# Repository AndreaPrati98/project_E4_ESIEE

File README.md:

# project_E4_ESIEE

The code for using the sensors and all is: _project_E4_ESIEE/Rendu_code/code_wio/code_final.wio/code_final.wio.ino_

The other files are experiments and trials to get the confidence with the WIO Terminal.

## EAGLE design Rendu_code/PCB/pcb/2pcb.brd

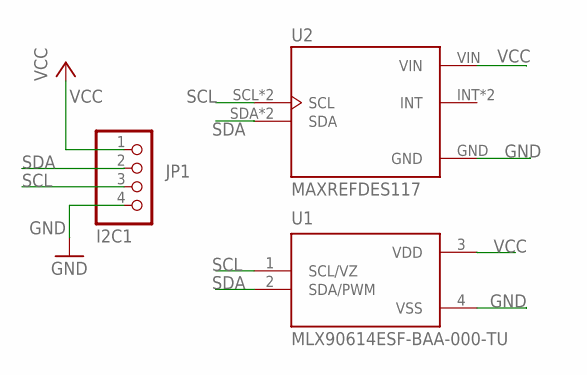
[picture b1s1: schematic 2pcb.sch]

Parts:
JP1: I2C1; 1X04/90
U1: MLX90614ESF-BAA-000-TU; TO254P942H425-4
U2: MAXREFDES117; MODULE_MAXREFDES117

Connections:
GND: JP1.4, U1.4 (VSS), U2.GND
SCL: JP1.3, U1.1 (SCL/VZ), U2.SCL, U2.SCL1 (SCL)
SDA: JP1.2, U1.2 (SDA/PWM), U2.SDA, U2.SDA1 (SDA)
VCC: JP1.1, U1.3 (VDD), U2.VIN

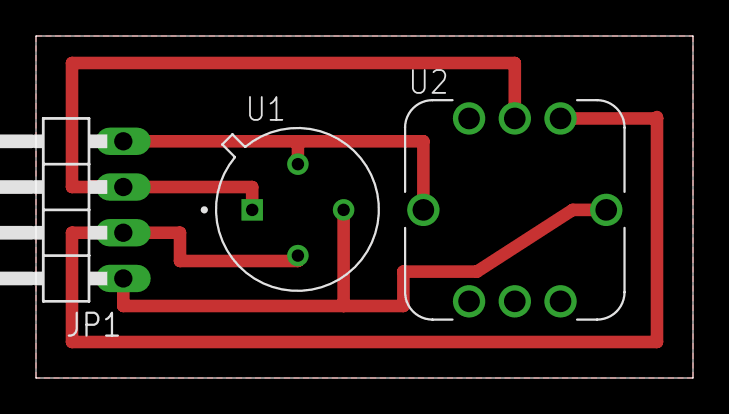
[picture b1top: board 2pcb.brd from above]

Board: 2 copper layers, 36.5 x 19.0 mm, 3 parts (0 on the bottom side), 4 nets.

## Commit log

2023-02-14 added libraries and prepared experiments
2023-02-17 added experiments and started to modify the main code
2023-02-17 added comments
2023-02-17 fixed the problem of the missed 'new line' on the Spo2 recording
2023-02-21 new code with more comments on the serial monitor and fixed csv
2023-03-06 small tries
2023-04-20 removed some old code and created code for showing how to enable bluetooth
